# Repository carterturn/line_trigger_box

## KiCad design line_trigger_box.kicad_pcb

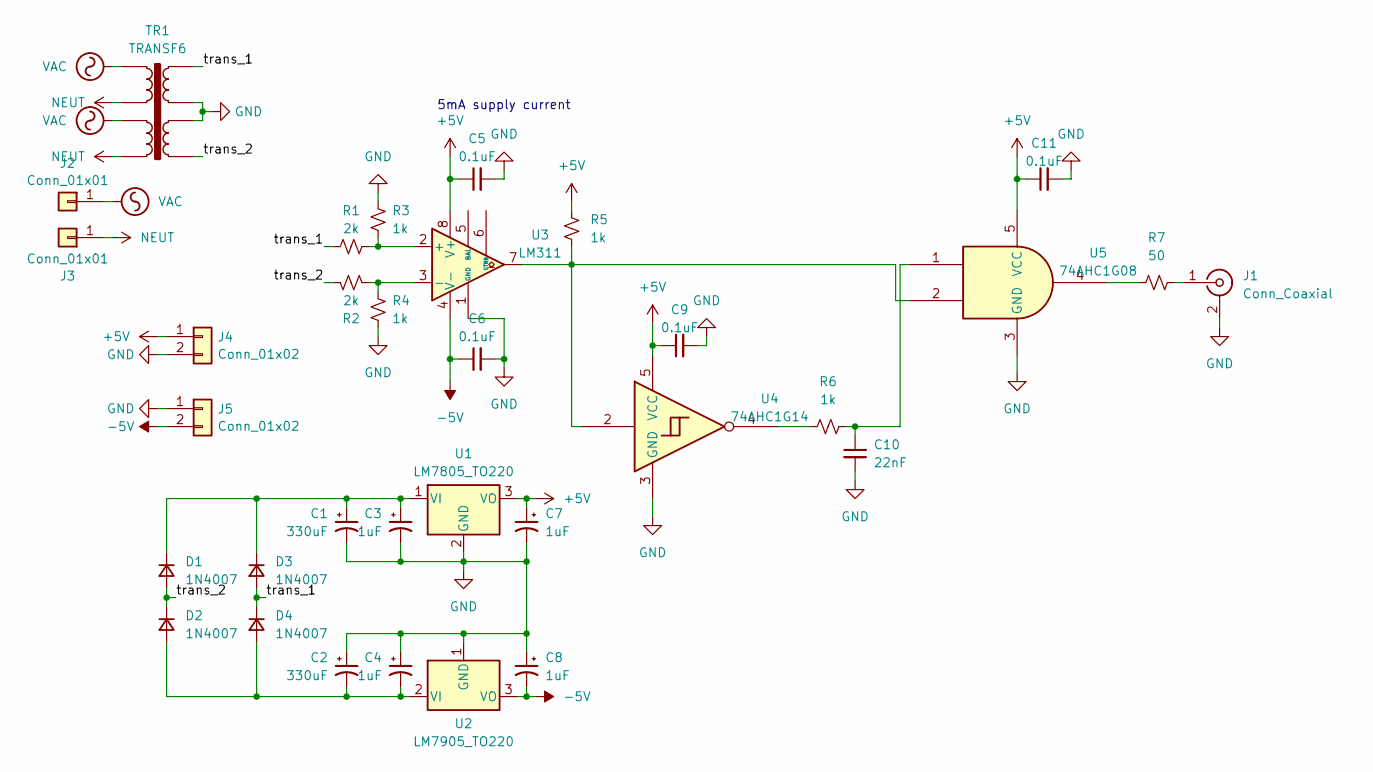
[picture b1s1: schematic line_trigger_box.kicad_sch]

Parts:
C1, C2: 330uF; CP_Radial_D10.0mm_P3.50mm
C3, C4, C7, C8: 1uF; CP_Radial_D5.0mm_P2.00mm
C5, C6, C9, C11: 0.1uF; C_0805_2012Metric
C10: 22nF; C_0805_2012Metric
D1, D2, D3, D4: 1N4007; D_DO-41_SOD81_P12.70mm_Horizontal
J1: Conn_Coaxial; BNC_Amphenol_B6252HB-NPP3G-50_Horizontal
J2, J3: Conn_01x01; PinSocket_1x01_P2.54mm_Vertical
J4, J5: Conn_01x02; PinSocket_1x02_P2.54mm_Vertical
R1, R2: 2k; R_0805_2012Metric
R3, R4, R5, R6: 1k; R_0805_2012Metric
R7: 50; R_0805_2012Metric
TR1: TRANSF6; L01-6301
U1: LM7805_TO220; TO-220-3_Vertical
U2: LM7905_TO220; TO-220-3_Vertical
U3: LM311; SOIC-8_3.9x4.9mm_P1.27mm
U4: 74AHC1G14; SOT-23-5
U5: 74AHC1G08; SOT-23-5

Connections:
+5V: C5.1, C7.1, C9.1, C11.1, J4.1, R5.1, U1.3 (VO), U3.8 (V+), U4.5 (VCC), U5.5 (VCC)
-5V: C6.1, C8.2, J5.2, U2.3 (VO), U3.4 (V-)
/trans_1: D3.2 (A), D4.1 (K), R1.1, TR1.8
/trans_2: D1.2 (A), D2.1 (K), R2.1, TR1.5
GND: C1.2, C2.1, C3.2, C4.1, C5.2, C6.2, C7.2, C8.1, C9.2, C10.2, C11.2, J1.2 (Ext), J4.2, J5.1, R3.1, R4.2, TR1.6, TR1.7, U1.2 (GND), U2.1 (GND), U3.1 (GND), U4.3 (GND), U5.3 (GND)
NEUT: J3.1, TR1.2, TR1.4
unnamed: C10.1, R6.2, U5.1
unnamed: C1.1, C3.1, D1.1 (K), D3.1 (K), U1.1 (VI)
unnamed: C2.2, C4.2, D2.2 (A), D4.2 (A), U2.2 (VI)
unnamed: J1.1 (In), R7.2
unnamed: R5.2, U3.7, U4.2, U5.2
unnamed: R6.1, U4.4
unnamed: R7.1, U5.4
unnamed: R1.2, R3.2, U3.2 (+)
unnamed: R2.2, R4.1, U3.3 (-)
VAC: J2.1, TR1.1, TR1.3

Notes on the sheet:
5mA supply current

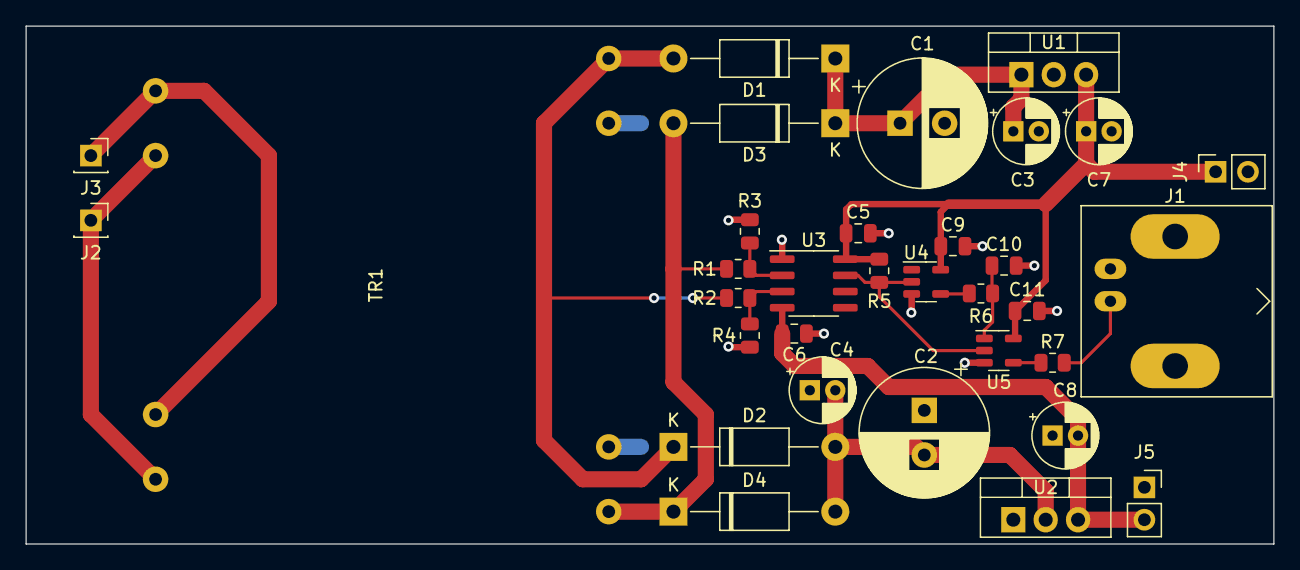
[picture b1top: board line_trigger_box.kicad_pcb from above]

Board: 2 copper layers, 97.9 x 40.6 mm, 33 parts (0 on the bottom side), 16 nets.

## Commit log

2024-02-06 Initial commit.
    Not version in Fermi2, issues with the transformer connection have been fixed.
